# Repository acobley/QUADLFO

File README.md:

# QUADLFO

This is a development project, it is not tested

It shows using a ATMEGA328 to produce upto 4 LFO signals.

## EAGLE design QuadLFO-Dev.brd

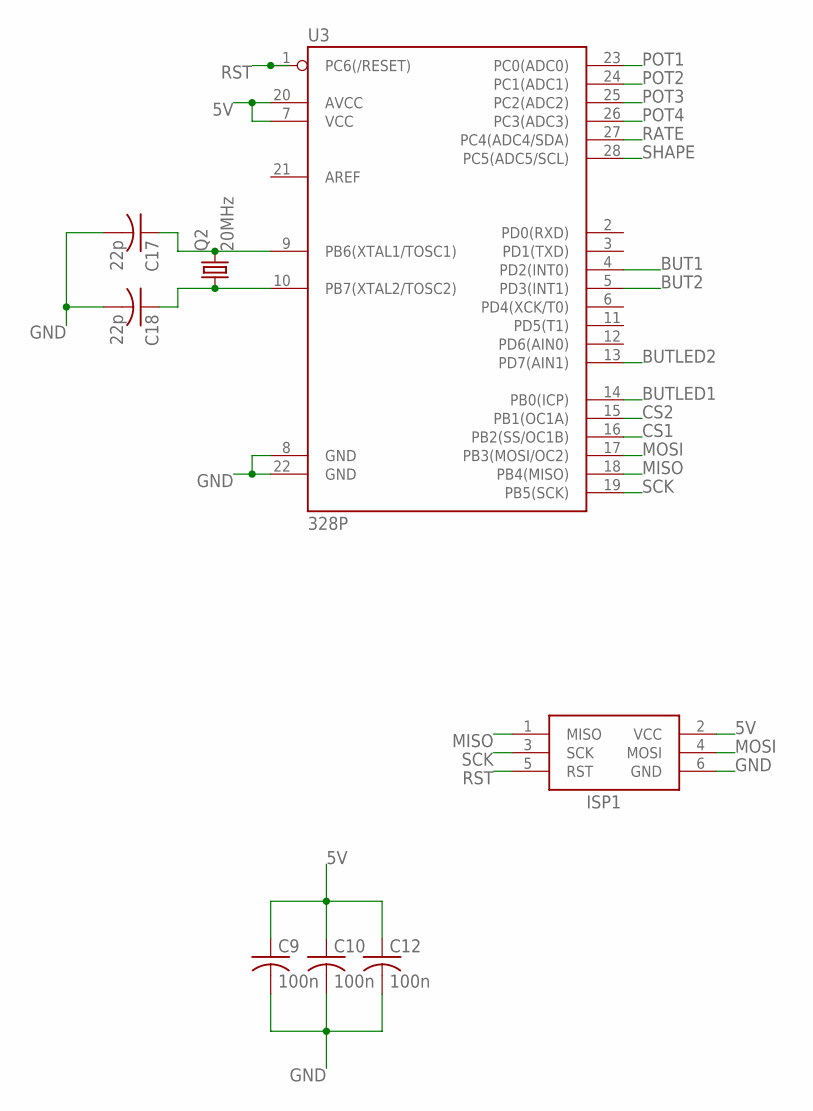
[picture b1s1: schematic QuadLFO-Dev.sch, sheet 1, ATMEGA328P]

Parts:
C9, C10, C12: 100n; C0805K
C17, C18: 22p; C0805K
ISP1: AVRISP-6; AVRISP
Q2: 20MHz; HC49UP
U3: 328P; DIP28

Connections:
5V: C9.1, C10.1, C12.1, ISP1.2 (VCC), U3.7 (VCC), U3.20 (AVCC); also elsewhere on the board
BUT1: U3.4 (PD2(INT0)); also elsewhere on the board
BUT2: U3.5 (PD3(INT1)); also elsewhere on the board
BUTLED1: U3.14 (PB0(ICP)); also elsewhere on the board
BUTLED2: U3.13 (PD7(AIN1)); also elsewhere on the board
CS1: U3.16 (PB2(SS/OC1B)); also elsewhere on the board
CS2: U3.15 (PB1(OC1A)); also elsewhere on the board
GND: C9.2, C10.2, C12.2, C17.2, C18.2, ISP1.6 (GND), U3.8 (GND), U3.22 (GND); also elsewhere on the board
MISO: ISP1.1 (MISO), U3.18 (PB4(MISO))
MOSI: ISP1.4 (MOSI), U3.17 (PB3(MOSI/OC2)); also elsewhere on the board
unnamed: C17.1, Q2.2, U3.9 (PB6(XTAL1/TOSC1))
unnamed: C18.1, Q2.1, U3.10 (PB7(XTAL2/TOSC2))
POT1: U3.23 (PC0(ADC0)); also elsewhere on the board
POT2: U3.24 (PC1(ADC1)); also elsewhere on the board
POT3: U3.25 (PC2(ADC2)); also elsewhere on the board
POT4: U3.26 (PC3(ADC3)); also elsewhere on the board
RATE: U3.27 (PC4(ADC4/SDA)); also elsewhere on the board
RST: ISP1.5 (RST), U3.1 (PC6(/RESET))
SCK: ISP1.3 (SCK), U3.19 (PB5(SCK)); also elsewhere on the board
SHAPE: U3.28 (PC5(ADC5/SCL)); also elsewhere on the board

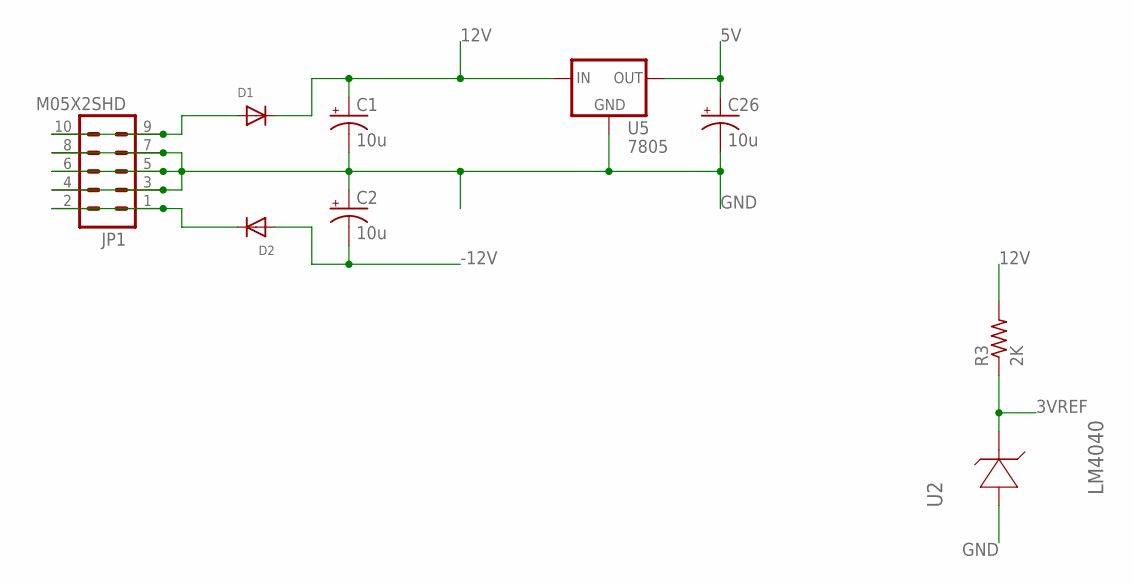
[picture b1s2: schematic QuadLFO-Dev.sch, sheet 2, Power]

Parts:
C1, C2, C26: 10u; 153CLV-0505
D1, D2: DIODESMA; SMADIODE
JP1: M05X2SHD; 2X5-SHROUDED
R3: 2K; R0805
U2: LM4040; SOT95P237X112-3N
U5: 7805; V-REG

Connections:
3VREF: R3.1, U2.1 (CATHODE); also elsewhere on the board
5V: C26.+, U5.3 (OUT); also elsewhere on the board
12V: C1.+, D1.C, R3.2, U5.1 (IN); also elsewhere on the board
-12V: C2.-, D2.A; also elsewhere on the board
GND: C1.-, C2.+, C26.-, JP1.3, JP1.4, JP1.5, JP1.6, JP1.7, JP1.8, U2.2 (ANODE), U5.4 (GND); also elsewhere on the board
unnamed: D2.C, JP1.1, JP1.2
unnamed: D1.A, JP1.9, JP1.10

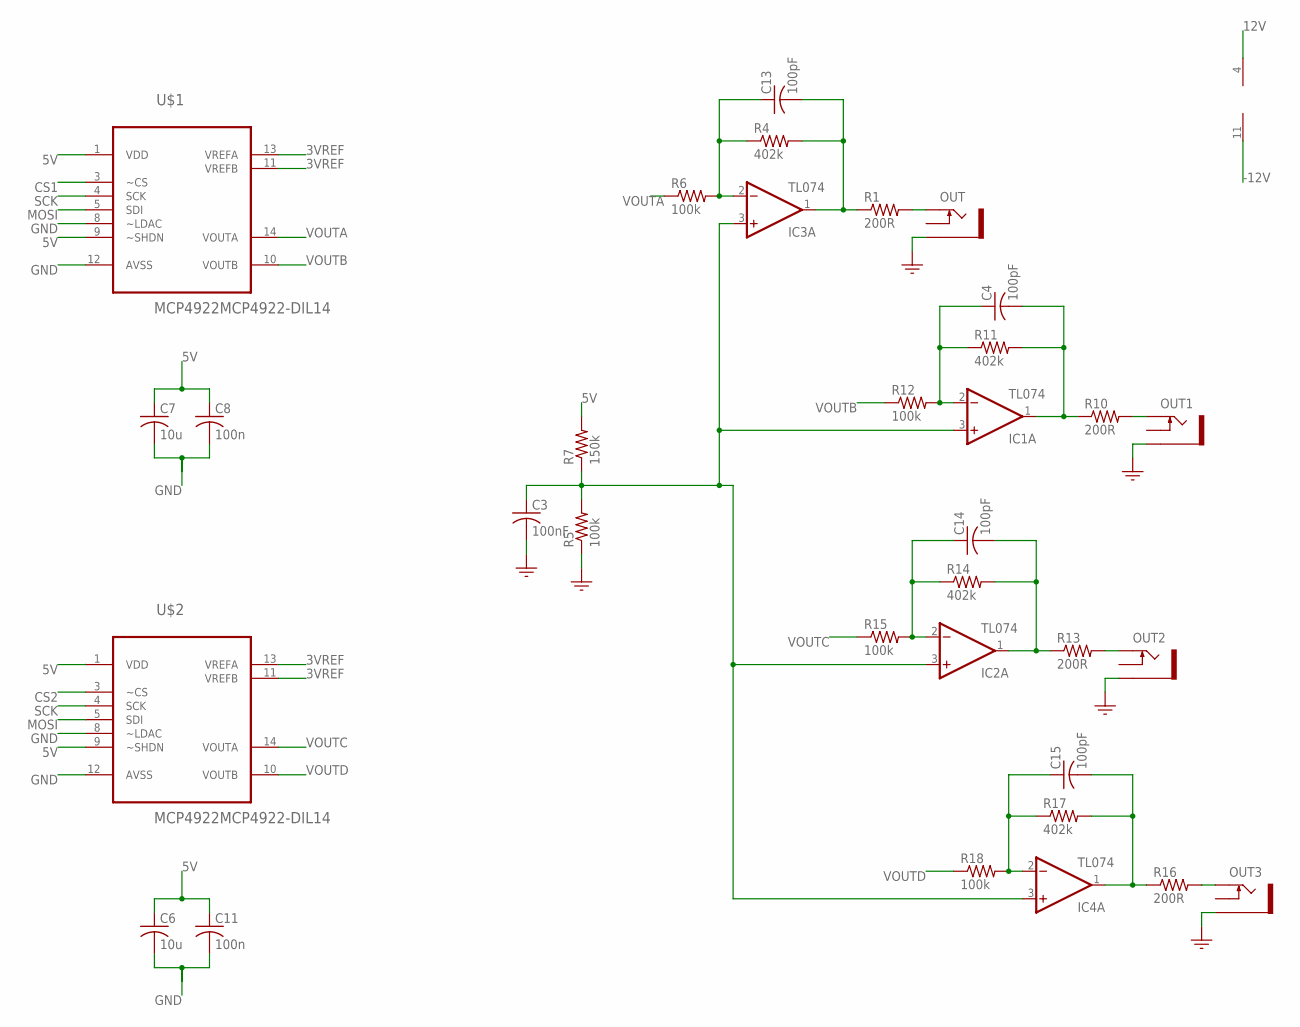
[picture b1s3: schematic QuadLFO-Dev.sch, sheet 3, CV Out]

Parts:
C3: 100nF; C0805
C4, C13, C14, C15: 100pF; C0805
C6, C7: 10u; C0805K
C8, C11: 100n; C0805K
IC1, IC2, IC3, IC4: TL074; SO14
OUT, OUT1, OUT2, OUT3: PJ301M-12
R1, R10, R13, R16: 200R; R0805
R4, R11, R14, R17: 402k; R0805
R5, R6, R12, R15, R18: 100k; R0805
R7: 150k; R0805
U$1, U$2: MCP4922MCP4922-DIL14; DIL14

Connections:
3VREF: U$1.11 (VREFB), U$1.13 (VREFA), U$2.11 (VREFB), U$2.13 (VREFA); also elsewhere on the board
5V: C6.1, C7.1, C8.1, C11.1, R7.2, U$1.1 (VDD), U$1.9 (~SHDN), U$2.1 (VDD), U$2.9 (~SHDN); also elsewhere on the board
12V: IC1.4 (V+); also elsewhere on the board
-12V: IC1.11 (V-); also elsewhere on the board
CS1: U$1.3 (~CS); also elsewhere on the board
CS2: U$2.3 (~CS); also elsewhere on the board
GND: C3.2, C6.2, C7.2, C8.2, C11.2, OUT.GND (SLEEVE), OUT1.GND (SLEEVE), OUT2.GND (SLEEVE), OUT3.GND (SLEEVE), R5.1, U$1.8 (~LDAC), U$1.12 (AVSS), U$2.8 (~LDAC), U$2.12 (AVSS); also elsewhere on the board
MOSI: U$1.5 (SDI), U$2.5 (SDI); also elsewhere on the board
unnamed: C13.2, IC3.1 (OUT), R1.1, R4.2
unnamed: OUT.TIP, R1.2
unnamed: C13.1, IC3.2 (-IN), R4.1, R6.2
unnamed: C4.2, IC1.1 (OUT), R10.1, R11.2
unnamed: OUT1.TIP, R10.2
unnamed: C4.1, IC1.2 (-IN), R11.1, R12.2
unnamed: C14.2, IC2.1 (OUT), R13.1, R14.2
unnamed: OUT2.TIP, R13.2
unnamed: C14.1, IC2.2 (-IN), R14.1, R15.2
unnamed: C15.2, IC4.1 (OUT), R16.1, R17.2
unnamed: OUT3.TIP, R16.2
unnamed: C3.1, IC1.3 (+IN), IC2.3 (+IN), IC3.3 (+IN), IC4.3 (+IN), R5.2, R7.1
unnamed: C15.1, IC4.2 (-IN), R17.1, R18.2
SCK: U$1.4 (SCK), U$2.4 (SCK); also elsewhere on the board
V+: IC2.4 (V+), IC3.4 (V+), IC4.4 (V+)
V-: IC2.11 (V-), IC3.11 (V-), IC4.11 (V-)
VOUTA: R6.1, U$1.14 (VOUTA)
VOUTB: R12.1, U$1.10 (VOUTB)
VOUTC: R15.1, U$2.14 (VOUTA)
VOUTD: R18.1, U$2.10 (VOUTB)

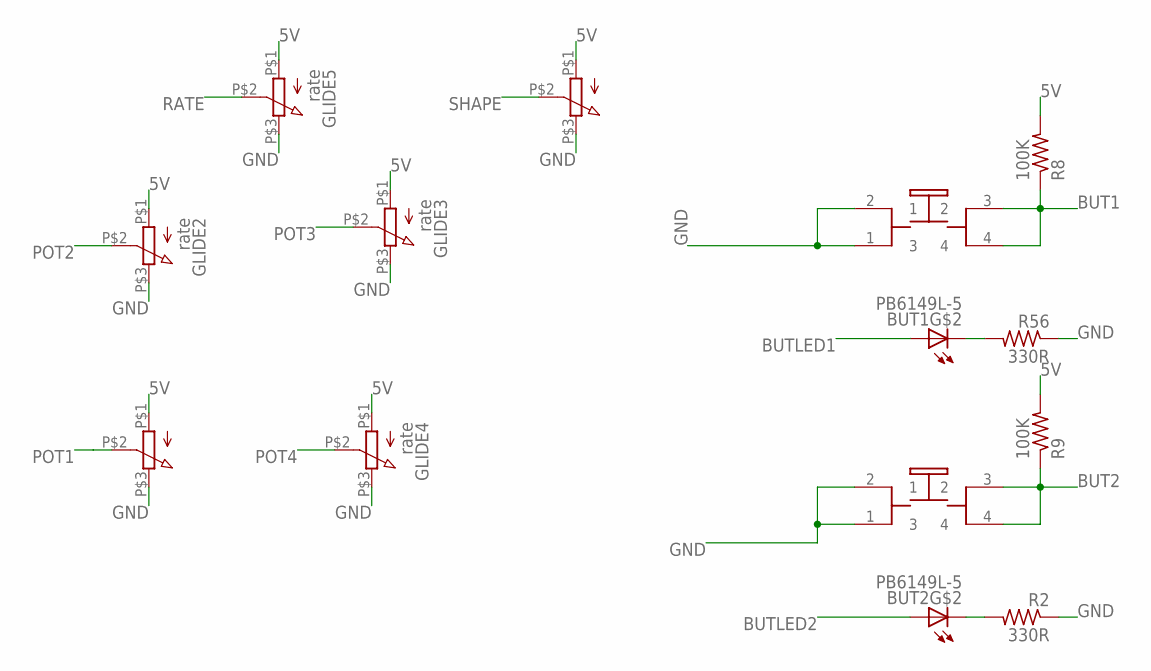
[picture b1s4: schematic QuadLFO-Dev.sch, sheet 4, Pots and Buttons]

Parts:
BUT1, BUT2: PB6149L-5; PB6149L
GLIDE1, GLIDE2, GLIDE3, GLIDE4, GLIDE5, GLIDE6: rate; POT
R2, R56: 330R; R0805
R8, R9: 100K; R0805

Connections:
5V: GLIDE1.P$1 (1), GLIDE2.P$1 (1), GLIDE3.P$1 (1), GLIDE4.P$1 (1), GLIDE5.P$1 (1), GLIDE6.P$1 (1), R8.2, R9.2; also elsewhere on the board
BUT1: BUT1.3 (2), BUT1.4, R8.1; also elsewhere on the board
BUT2: BUT2.3 (2), BUT2.4, R9.1; also elsewhere on the board
BUTLED1: BUT1.A; also elsewhere on the board
BUTLED2: BUT2.A; also elsewhere on the board
GND: BUT1.1 (3), BUT1.2 (1), BUT2.1 (3), BUT2.2 (1), GLIDE1.P$3 (3), GLIDE2.P$3 (3), GLIDE3.P$3 (3), GLIDE4.P$3 (3), GLIDE5.P$3 (3), GLIDE6.P$3 (3), R2.1, R56.1; also elsewhere on the board
unnamed: BUT2.K (C), R2.2
unnamed: BUT1.K (C), R56.2
POT1: GLIDE1.P$2 (2); also elsewhere on the board
POT2: GLIDE2.P$2 (2); also elsewhere on the board
POT3: GLIDE3.P$2 (2); also elsewhere on the board
POT4: GLIDE4.P$2 (2); also elsewhere on the board
RATE: GLIDE5.P$2 (2); also elsewhere on the board
SHAPE: GLIDE6.P$2 (2); also elsewhere on the board

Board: 2 copper layers, 62 parts (0 on the bottom side), 46 nets, no tracks yet.

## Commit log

2019-03-16 Added Schematic file
2019-03-16 changed to &4 seris op amps

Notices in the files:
parts and their libraries:
SparkFun-Connectors: Licensing: CC v3.0 Share-Alike You are welcome to use this library for commercial purposes.
SparkFun-IC-Microcontroller: Licensing: Creative Commons ShareAlike 4.0 International - https://creativecommons.org/licenses/by-sa/4.0
